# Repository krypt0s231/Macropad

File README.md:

# KRYPT's Hackpad – Custom 4×4 KMK Macropad with OLED & RGB

A custom-designed 4×4 mechanical macropad built around the Seeed XIAO RP2040, featuring:

Matrix-scanned mechanical switches with diodes

SK6812 Mini RGB LEDs

0.91" OLED display

KMK firmware (CircuitPython)

PC-side system monitoring (CPU / RAM / GPU / Disk)

This project was designed as a DIY / competition-grade hackpad, from schematic → PCB → firmware → case.

# Project Images

  ## **Schematic**

  ## **PCB Layout**

  ## **Case & Assembly**

# Hardware Overview

MCU: Seeed Studio XIAO RP2040

Switches: MX-style mechanical switches

Matrix: 4 Rows × 4 Columns with 1N4148 diodes

RGB: SK6812 Mini (NeoPixel compatible)

Display: 0.91" OLED (SSD1306, 128×32)

Power: USB-C

# Pin Mapping
***Matrix***

**Columns**

COL0 → GPIO0

COL1 → GPIO27

COL2 → GPIO28

COL3 → GPIO29

**Rows**

ROW0 → GPIO3

ROW1 → GPIO4

ROW2 → GPIO2

ROW3 → GPIO1

**Peripherals**

RGB Data: GPIO26

OLED: I²C (default XIAO pins)

# Firmware

Keyboard firmware: KMK (CircuitPython)

Features:

Matrix scanning

RGB underglow

OLED display

USB HID data input from PC

#The OLED displays:

 CPU usage

 RAM usage

 GPU usage

 Disk (C:) usage

System statistics are sent from a PC-side Python script over USB HID.

# PC-side Software

A Python helper script runs on the host computer to:

Read system stats (via psutil, GPUtil)

Send data to the keyboard using HID

This architecture is similar to Stream Decks and professional macro pads.

# Author

Designed and built by kryptos

License

Open-sourse

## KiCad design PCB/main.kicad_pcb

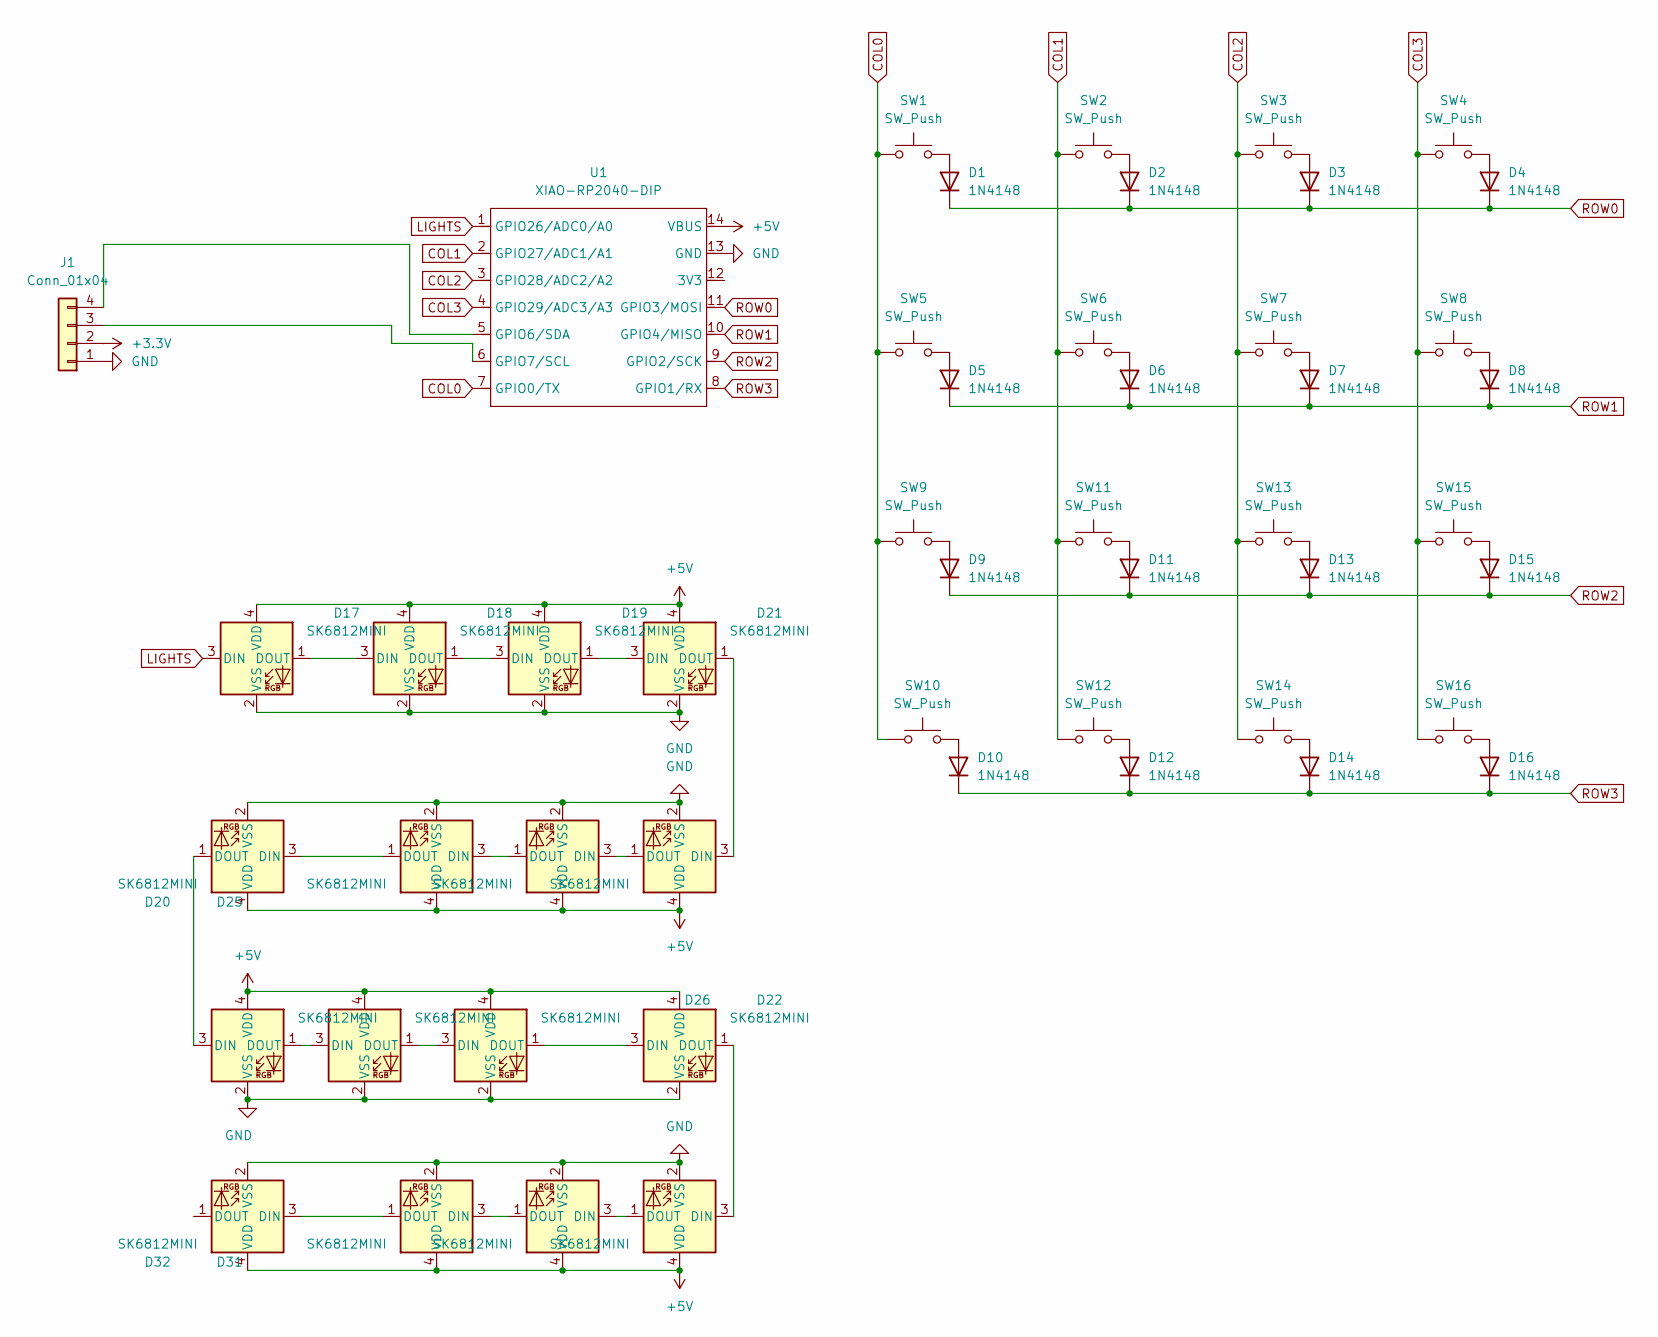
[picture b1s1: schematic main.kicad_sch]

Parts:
D1, D2, D3, D4, D5, D6, D7, D8, D9, D10, D11, D12, D13, D14, D15, D16: 1N4148; D_DO-35_SOD27_P7.62mm_Horizontal
D17, D18, D19, D20, D21, D22, D23, D24, D25, D26, D27, D28, D29, D30, D31, D32: SK6812MINI; MX_SK6812MINI-E_REV
J1: Conn_01x04; SSD1306-0.91-OLED-4pin-128x32
SW1, SW2, SW3, SW4, SW5, SW6, SW7, SW8, SW9, SW10, SW11, SW12, SW13, SW14, SW15, SW16: SW_Push; SW_Cherry_MX_1.00u_PCB
U1: XIAO-RP2040-DIP

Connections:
+3.3V: J1.2
+5V: D17.4 (VDD), D18.4 (VDD), D19.4 (VDD), D20.4 (VDD), D21.4 (VDD), D22.4 (VDD), D23.4 (VDD), D24.4 (VDD), D25.4 (VDD), D26.4 (VDD), D27.4 (VDD), D28.4 (VDD), D29.4 (VDD), D30.4 (VDD), D31.4 (VDD), D32.4 (VDD), U1.14 (VBUS)
COL0: SW1.1, SW5.1, SW9.1, SW10.1, U1.7 (GPIO0/TX)
COL1: SW2.1, SW6.1, SW11.1, SW12.1, U1.2 (GPIO27/ADC1/A1)
COL2: SW3.1, SW7.1, SW13.1, SW14.1, U1.3 (GPIO28/ADC2/A2)
COL3: SW4.1, SW8.1, SW15.1, SW16.1, U1.4 (GPIO29/ADC3/A3)
GND: D17.2 (VSS), D18.2 (VSS), D19.2 (VSS), D20.2 (VSS), D21.2 (VSS), D22.2 (VSS), D23.2 (VSS), D24.2 (VSS), D25.2 (VSS), D26.2 (VSS), D27.2 (VSS), D28.2 (VSS), D29.2 (VSS), D30.2 (VSS), D31.2 (VSS), D32.2 (VSS), J1.1, U1.13 (GND)
LIGHTS: D17.3 (DIN), U1.1 (GPIO26/ADC0/A0)
unnamed: D1.2 (A), SW1.2
unnamed: D2.2 (A), SW2.2
unnamed: D3.2 (A), SW3.2
unnamed: D4.2 (A), SW4.2
unnamed: D5.2 (A), SW5.2
unnamed: D6.2 (A), SW6.2
unnamed: D7.2 (A), SW7.2
unnamed: D8.2 (A), SW8.2
unnamed: D9.2 (A), SW9.2
unnamed: D10.2 (A), SW10.2
unnamed: D11.2 (A), SW11.2
unnamed: D12.2 (A), SW12.2
unnamed: D13.2 (A), SW13.2
unnamed: D14.2 (A), SW14.2
unnamed: D15.2 (A), SW15.2
unnamed: D16.2 (A), SW16.2
unnamed: D17.1 (DOUT), D18.3 (DIN)
unnamed: D18.1 (DOUT), D19.3 (DIN)
unnamed: D19.1 (DOUT), D21.3 (DIN)
unnamed: D20.3 (DIN), D25.1 (DOUT)
unnamed: D20.1 (DOUT), D28.3 (DIN)
unnamed: D21.1 (DOUT), D23.3 (DIN)
unnamed: D22.3 (DIN), D26.1 (DOUT)
unnamed: D22.1 (DOUT), D29.3 (DIN)
unnamed: D23.1 (DOUT), D24.3 (DIN)
unnamed: D24.1 (DOUT), D25.3 (DIN)
unnamed: D26.3 (DIN), D27.1 (DOUT)
unnamed: D27.3 (DIN), D28.1 (DOUT)
unnamed: D29.1 (DOUT), D30.3 (DIN)
unnamed: D30.1 (DOUT), D31.3 (DIN)
unnamed: D31.1 (DOUT), D32.3 (DIN)
unnamed: J1.3, U1.6 (GPIO7/SCL)
unnamed: J1.4, U1.5 (GPIO6/SDA)
ROW0: D1.1 (K), D2.1 (K), D3.1 (K), D4.1 (K), U1.11 (GPIO3/MOSI)
ROW1: D5.1 (K), D6.1 (K), D7.1 (K), D8.1 (K), U1.10 (GPIO4/MISO)
ROW2: D9.1 (K), D11.1 (K), D13.1 (K), D15.1 (K), U1.9 (GPIO2/SCK)
ROW3: D10.1 (K), D12.1 (K), D14.1 (K), D16.1 (K), U1.8 (GPIO1/RX)

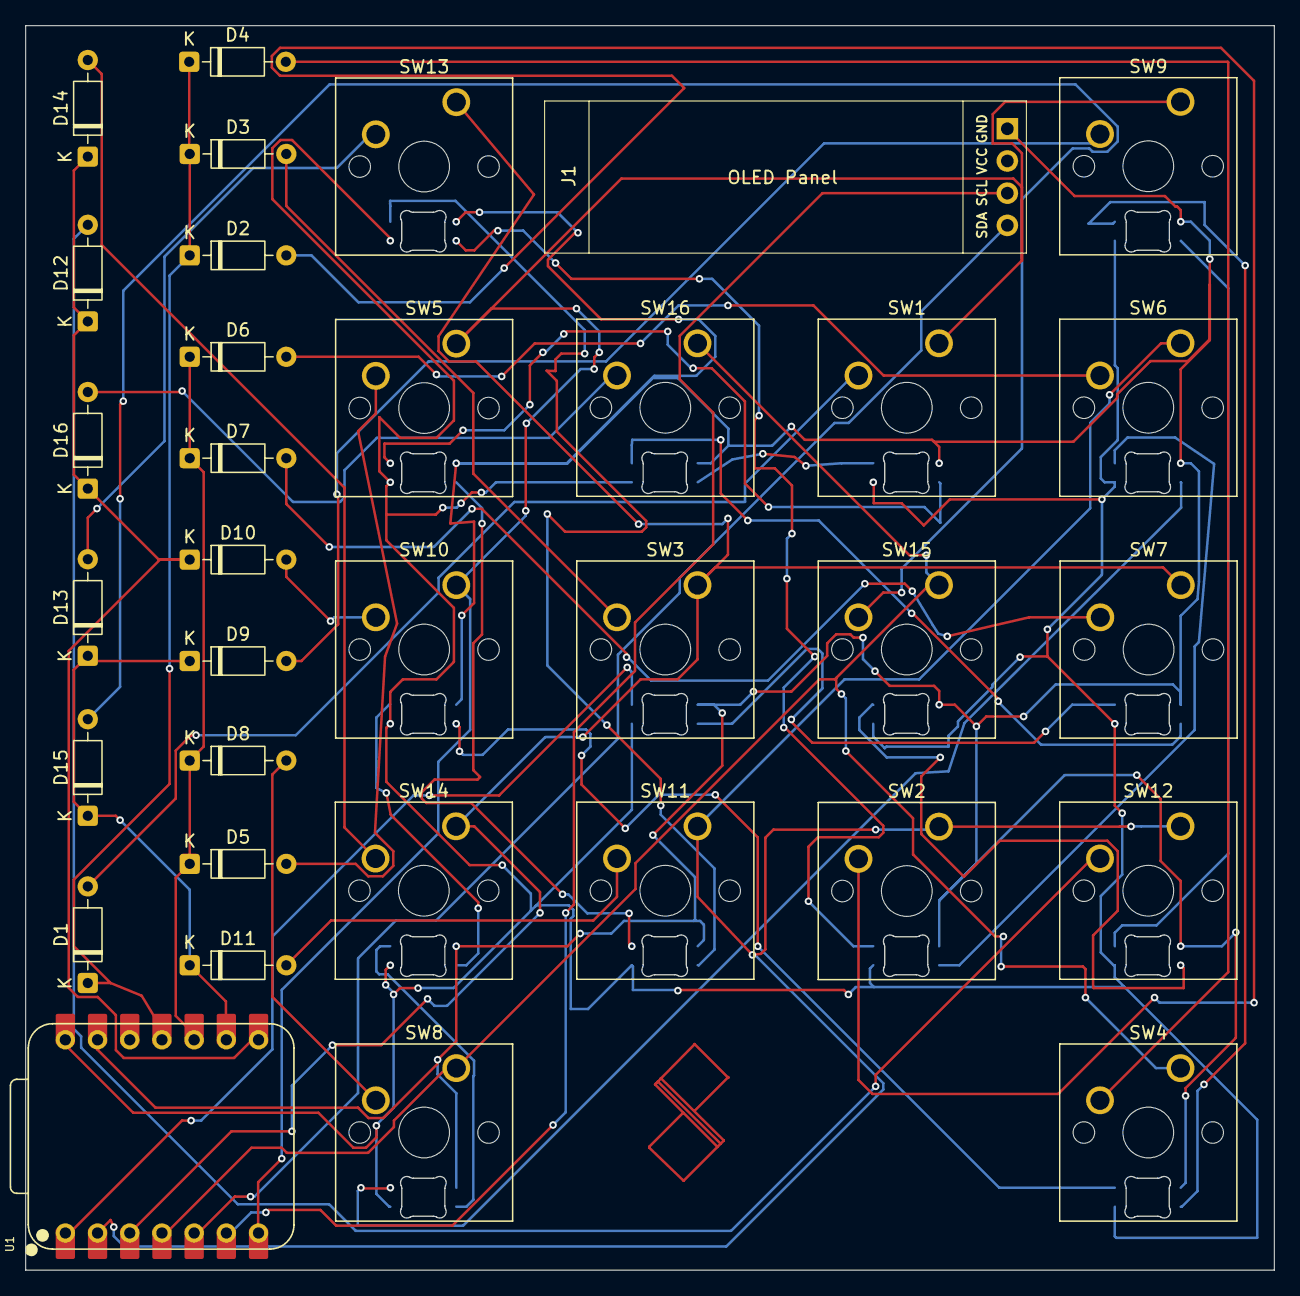
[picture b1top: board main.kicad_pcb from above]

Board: 2 copper layers, 98.5 x 98.2 mm, 50 parts (0 on the bottom side), 44 nets.

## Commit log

2025-12-26 Add README
